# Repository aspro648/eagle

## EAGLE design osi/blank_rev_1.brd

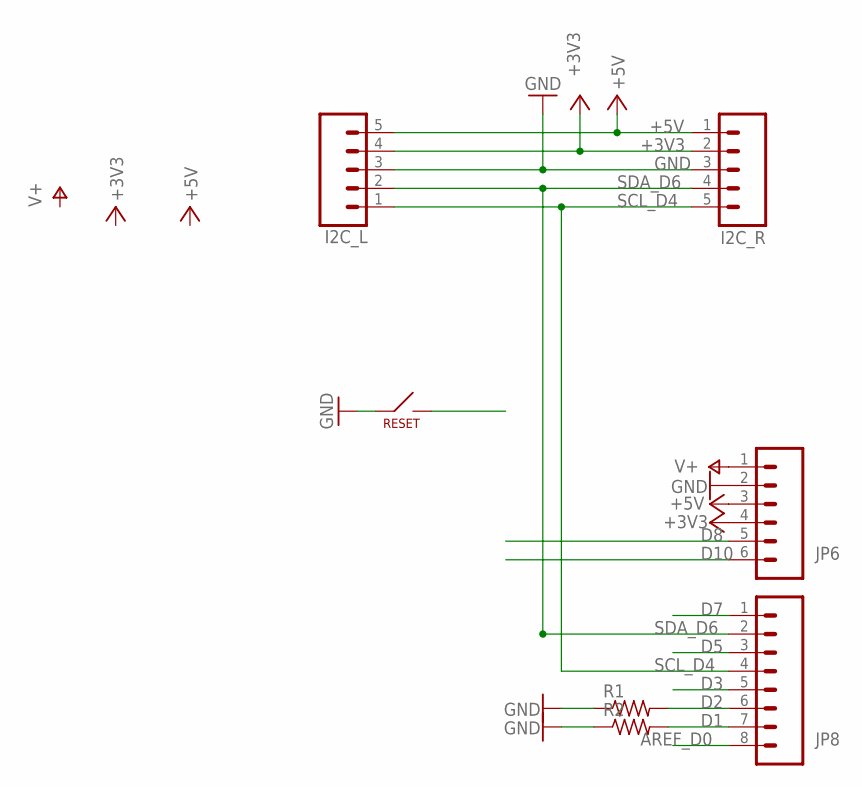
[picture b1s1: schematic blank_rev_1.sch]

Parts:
I2C_L, I2C_R: M05PTH; 1X05
JP6: M06SIP; 1X06
JP8: M081X08; 1X08
R1, R2: R-US_0204/2V; 0204V
RESET: PTS635_SWITCH

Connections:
+3V3: I2C_L.4, I2C_R.2, JP6.4
+5V: I2C_L.5, I2C_R.1, JP6.3
AREF_D0: JP8.8
D1: JP8.7, R2.2
D2: JP8.6, R1.2
D3: JP8.5
D5: JP8.3
D7: JP8.1
D8: JP6.5
D10: JP6.6
GND: I2C_L.3, I2C_R.3, JP6.2, R1.1, R2.1, RESET.P$1
RESET: RESET.P$2
SCL_D4: I2C_L.1, I2C_R.5, JP8.4
SDA_D6: I2C_L.2, I2C_R.4, JP8.2
V+: JP6.1

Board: 2 copper layers, 7 parts (0 on the bottom side), 7 nets, no tracks yet.

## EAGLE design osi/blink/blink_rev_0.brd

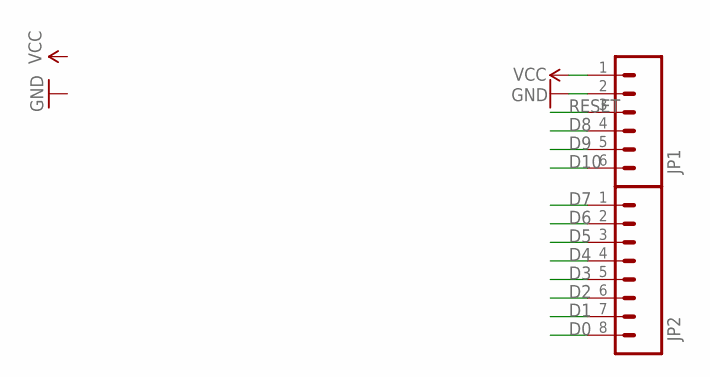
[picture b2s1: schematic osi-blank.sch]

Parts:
JP1: M06SIP; 1X06
JP2: M081X08; 1X08

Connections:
D0: JP2.8; also elsewhere on the board
D1: JP2.7; also elsewhere on the board
D2: JP2.6
D3: JP2.5
D4: JP2.4
D5: JP2.3; also elsewhere on the board
D6: JP2.2; also elsewhere on the board
D7: JP2.1; also elsewhere on the board
D8: JP1.4; also elsewhere on the board
D9: JP1.5
D10: JP1.6
GND: JP1.2; also elsewhere on the board
RESET: JP1.3
VCC: JP1.1; also elsewhere on the board

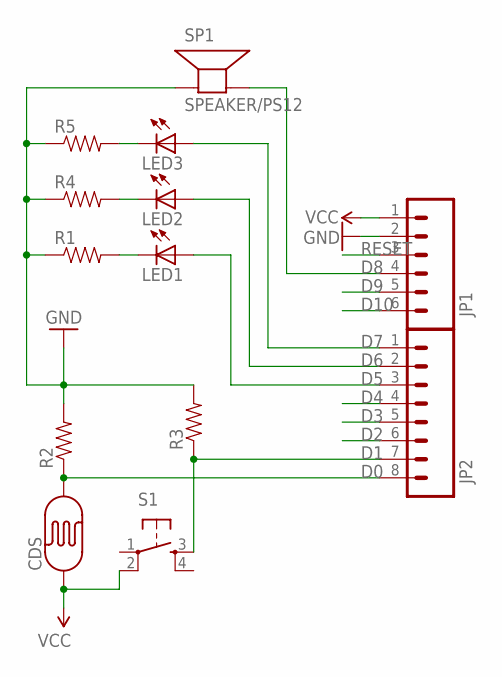
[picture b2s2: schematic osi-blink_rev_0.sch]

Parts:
CDS: PHOTOCELLPTH-KIT; PHOTOCELL-KIT
JP1: M06SIP; 1X06
JP2: M081X08; 1X08
LED1, LED2, LED3: LED3MM
R1, R2, R3, R4, R5: RESISTORKIT; AXIAL-0.3-KIT
S1: TAC_SWITCHPTH; TACTILE-PTH
SP1: SPEAKER/PS12; PS12

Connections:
D0: CDS.2, JP2.8, R2.P$1 (1)
D1: JP2.7, R3.P$1 (1), S1.3
D2: JP2.6
D3: JP2.5
D4: JP2.4
D5: JP2.3, LED1.A
D6: JP2.2, LED2.A
D7: JP2.1, LED3.A
D8: JP1.4, SP1.P$2 (-)
D9: JP1.5
D10: JP1.6
GND: JP1.2, R1.P$1 (1), R2.P$2 (2), R3.P$2 (2), R4.P$1 (1), R5.P$1 (1), SP1.P$1 (+)
unnamed: LED1.K (C), R1.P$2 (2)
unnamed: LED2.K (C), R4.P$2 (2)
unnamed: LED3.K (C), R5.P$2 (2)
RESET: JP1.3
VCC: CDS.1, JP1.1, S1.2

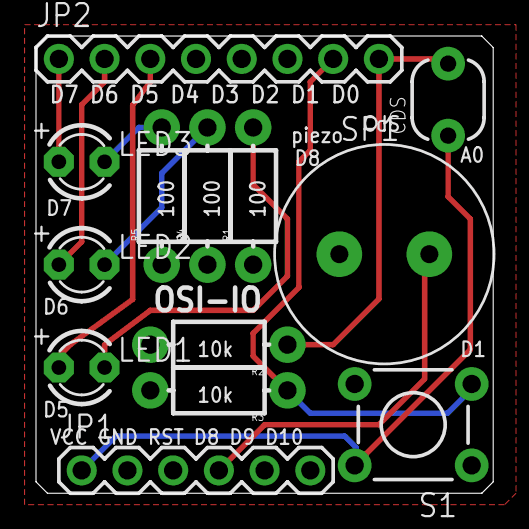
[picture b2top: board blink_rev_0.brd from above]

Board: 2 copper layers, 25.4 x 25.4 mm, 13 parts (0 on the bottom side), 11 nets.

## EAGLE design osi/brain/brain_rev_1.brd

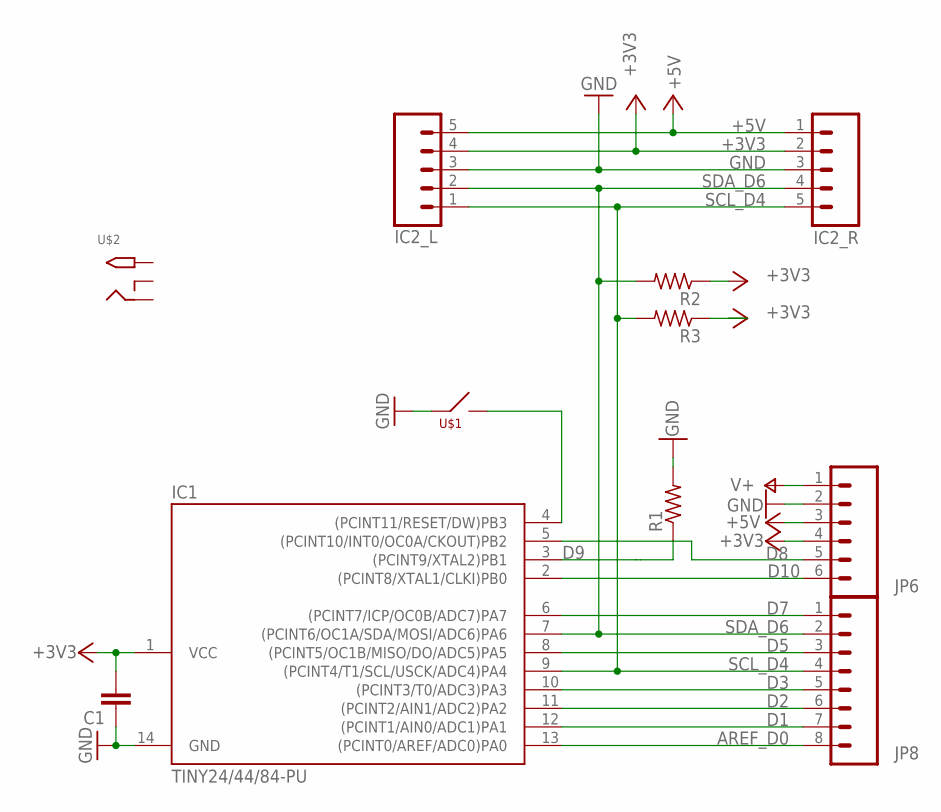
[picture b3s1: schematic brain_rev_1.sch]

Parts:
C1: CAPKIT; CAP-PTH-SMALL-KIT
IC1: TINY24/44/84-PU; DIL14
IC2_L, IC2_R: M05PTH; 1X05
JP6: M06SIP; 1X06
JP8: M081X08; 1X08
R1, R2, R3: R-US_0204/2V; 0204V
U$1: PTS635_SWITCH
U$2: 2.1MMJACKTHM; PJ-102A

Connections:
+3V3: C1.2, IC1.1 (VCC), IC2_L.4, IC2_R.2, JP6.4, R2.1, R3.1
+5V: IC2_L.5, IC2_R.1, JP6.3
AREF_D0: IC1.13 ((PCINT0/AREF/ADC0)PA0), JP8.8
D1: IC1.12 ((PCINT1/AIN0/ADC1)PA1), JP8.7
D2: IC1.11 ((PCINT2/AIN1/ADC2)PA2), JP8.6
D3: IC1.10 ((PCINT3/T0/ADC3)PA3), JP8.5
D5: IC1.8 ((PCINT5/OC1B/MISO/DO/ADC5)PA5), JP8.3
D7: IC1.6 ((PCINT7/ICP/OC0B/ADC7)PA7), JP8.1
D8: IC1.5 ((PCINT10/INT0/OC0A/CKOUT)PB2), JP6.5
D9: IC1.3 ((PCINT9/XTAL2)PB1), R1.1
D10: IC1.2 ((PCINT8/XTAL1/CLKI)PB0), JP6.6
GND: C1.1, IC1.14 (GND), IC2_L.3, IC2_R.3, JP6.2, R1.2, U$1.P$1
RESET: IC1.4 ((PCINT11/RESET/DW)PB3), U$1.P$2
SCL_D4: IC1.9 ((PCINT4/T1/SCL/USCK/ADC4)PA4), IC2_L.1, IC2_R.5, JP8.4, R3.2
SDA_D6: IC1.7 ((PCINT6/OC1A/SDA/MOSI/ADC6)PA6), IC2_L.2, IC2_R.4, JP8.2, R2.2
V+: JP6.1

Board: 2 copper layers, 11 parts (0 on the bottom side), 15 nets, no tracks yet.

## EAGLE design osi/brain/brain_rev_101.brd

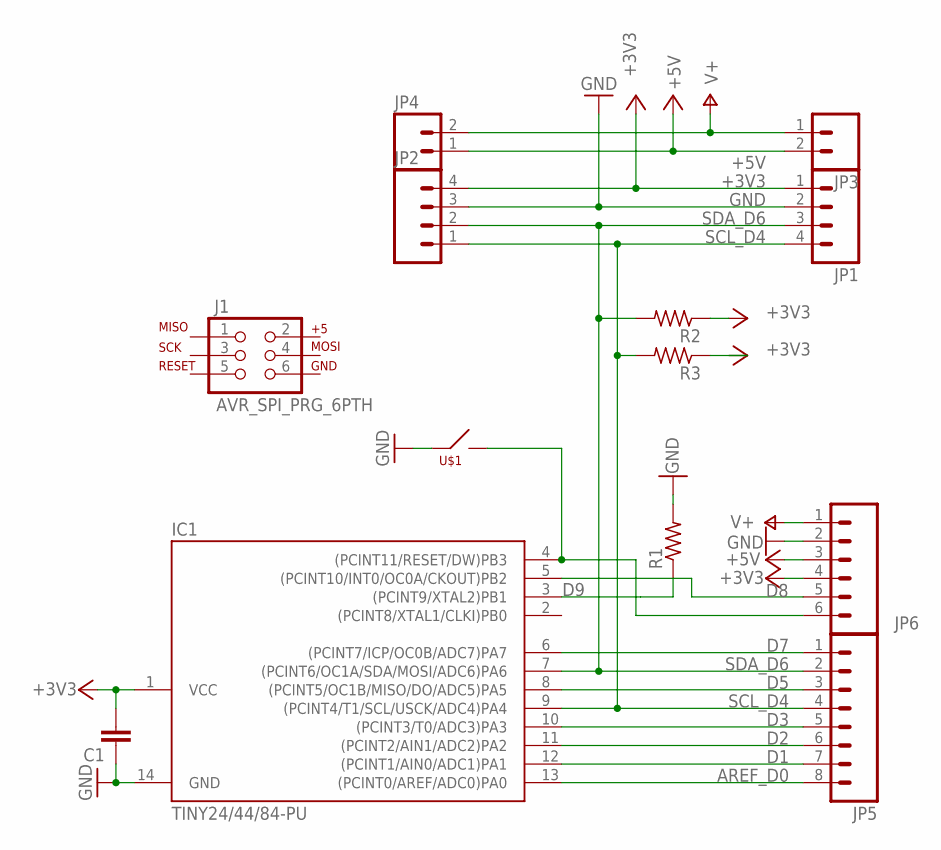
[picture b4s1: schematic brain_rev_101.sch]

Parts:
C1: CAPKIT; CAP-PTH-SMALL-KIT
IC1: TINY24/44/84-PU; DIL14
J1: AVR_SPI_PRG_6PTH; 2X3
JP1, JP2: M04PTH; 1X04
JP3, JP4: M02PTH; 1X02
JP5: M081X08; 1X08
JP6: M06SIP; 1X06
R1, R2, R3: R-US_0204/2V; 0204V
U$1: PTS635_SWITCH

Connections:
+3V3: C1.2, IC1.1 (VCC), JP1.1, JP2.4, JP6.4, R2.1, R3.1
+5V: JP3.2, JP4.1, JP6.3
AREF_D0: IC1.13 ((PCINT0/AREF/ADC0)PA0), JP5.8
D1: IC1.12 ((PCINT1/AIN0/ADC1)PA1), JP5.7
D2: IC1.11 ((PCINT2/AIN1/ADC2)PA2), JP5.6
D3: IC1.10 ((PCINT3/T0/ADC3)PA3), JP5.5
D5: IC1.8 ((PCINT5/OC1B/MISO/DO/ADC5)PA5), JP5.3
D7: IC1.6 ((PCINT7/ICP/OC0B/ADC7)PA7), JP5.1
D8: IC1.5 ((PCINT10/INT0/OC0A/CKOUT)PB2), JP6.5
D9: IC1.3 ((PCINT9/XTAL2)PB1), R1.1
GND: C1.1, IC1.14 (GND), JP1.2, JP2.3, JP6.2, R1.2, U$1.P$1
RESET: IC1.4 ((PCINT11/RESET/DW)PB3), JP6.6, U$1.P$2
SCL_D4: IC1.9 ((PCINT4/T1/SCL/USCK/ADC4)PA4), JP1.4, JP2.1, JP5.4, R3.2
SDA_D6: IC1.7 ((PCINT6/OC1A/SDA/MOSI/ADC6)PA6), JP1.3, JP2.2, JP5.2, R2.2
V+: JP3.1, JP4.2, JP6.1

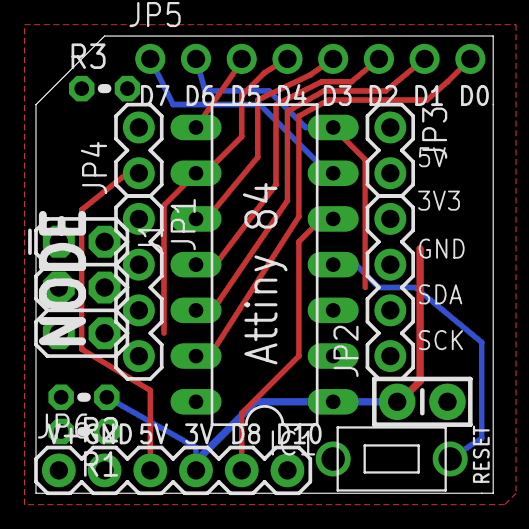
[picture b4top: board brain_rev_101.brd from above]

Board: 2 copper layers, 25.4 x 25.4 mm, 13 parts (0 on the bottom side), 15 nets.

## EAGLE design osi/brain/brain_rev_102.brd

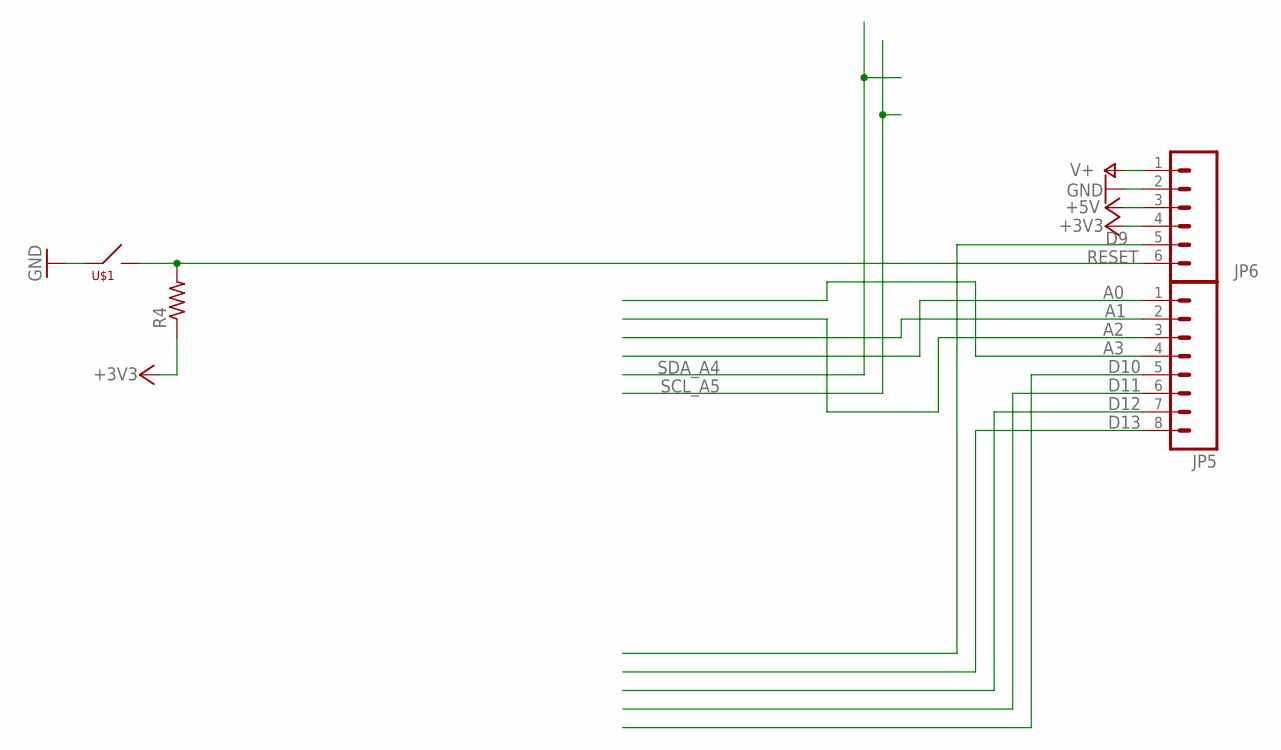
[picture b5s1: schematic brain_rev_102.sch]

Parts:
JP5: M081X08; 1X08
JP6: M06SIP; 1X06
R4: R-US_0204/2V; 0204V
U$1: PTS635_SWITCH

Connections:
+3V3: JP6.4, R4.1
+5V: JP6.3
A0: JP5.4
A1: JP5.3
A2: JP5.2
A3: JP5.1
D9: JP6.5
D10: JP5.8
D11: JP5.7
D12: JP5.6
D13: JP5.5
GND: JP6.2, U$1.P$1
RESET: JP6.6, R4.2, U$1.P$2
V+: JP6.1

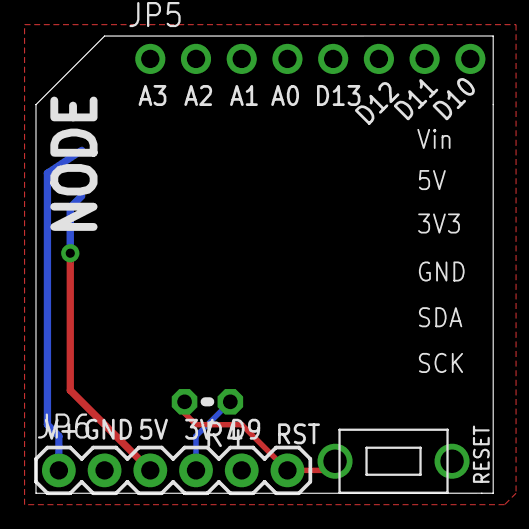
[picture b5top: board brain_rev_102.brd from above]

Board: 2 copper layers, 25.4 x 25.4 mm, 4 parts (0 on the bottom side), 3 nets.

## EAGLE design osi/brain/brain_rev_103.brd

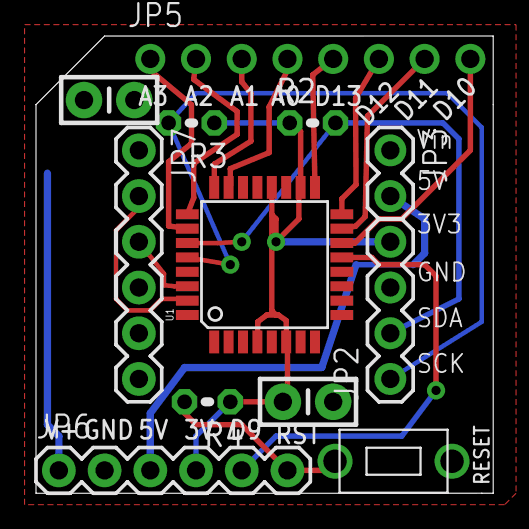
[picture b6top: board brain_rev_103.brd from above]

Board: 2 copper layers, 25.4 x 25.4 mm, 12 parts (0 on the bottom side), 19 nets.

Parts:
C1, C2: CAP-PTH-SMALL-KIT
JP2: 1X04
JP3: 1X02
JP5: 1X08
JP6: 1X06
JP7: FTDI Basic; 1X06
R2, R3, R4: 0204V
U1: ATMEGA168; TQFP32-08
U$1: PTS635_SWITCH

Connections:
+3V3: C1.2, JP2.4, JP6.4, JP7.4, R2.1, R3.1, R4.1, U1.4, U1.6, U1.18, U1.20
+5V: JP3.2, JP6.3
A0: JP5.4, U1.23
A1: JP5.3, U1.24
A2: JP5.2, U1.25
A3: JP5.1, U1.26
D9: JP6.5, U1.13
D10: JP5.8, U1.14
D11: JP5.7, U1.15
D12: JP5.6, U1.16
D13: JP5.5, U1.17
DTR: C2.2, JP7.1
GND: C1.1, JP2.3, JP6.2, JP7.5, JP7.6, U1.3, U1.5, U1.21, U$1.P$1
RESET: C2.1, JP6.6, R4.2, U1.29, U$1.P$2
RXI: JP7.3, U1.30
SCL_A5: JP2.1, R3.2, U1.28
SDA_A4: JP2.2, R2.2, U1.27
TXO: JP7.2, U1.31
V+: JP3.1, JP6.1

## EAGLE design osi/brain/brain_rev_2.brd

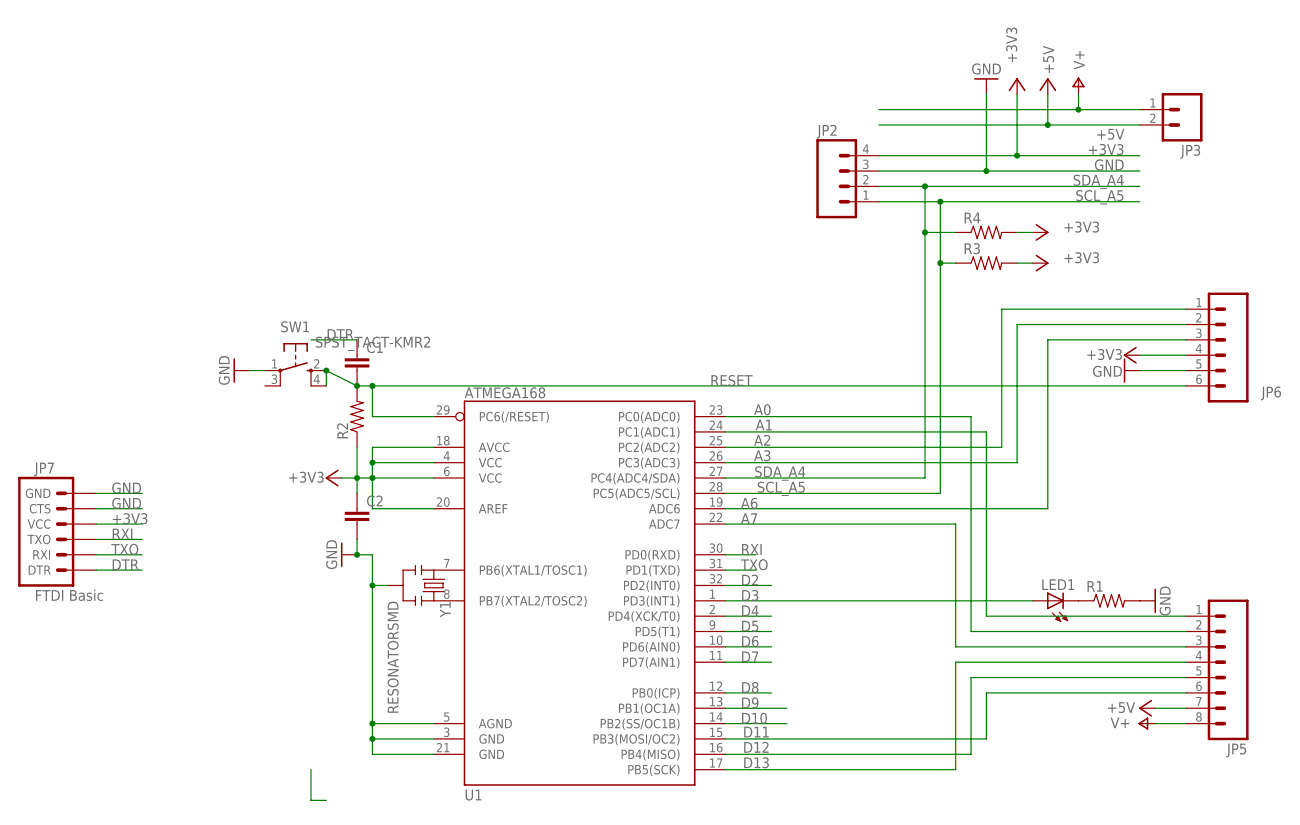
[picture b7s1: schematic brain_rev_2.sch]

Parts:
C1, C2: CAP1206; 1206
JP2: M04PTH; 1X04
JP3: M02PTH; 1X02
JP5: M081X08; 1X08
JP6: M06SIP; 1X06
JP7: FTDI Basic; 1X06
LED1: LEDCHIPLED_1206; CHIPLED_1206
R1, R2, R3, R4: RESISTOR1206; 1206
SW1: SPST_TACT-KMR2; KMR2
U1: ATMEGA168; TQFP32-08
Y1: RESONATORSMD; RESONATOR-SMD

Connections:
+3V3: C2.1, JP2.4, JP6.4, JP7.4 (VCC), R2.1, R3.2, R4.2, U1.4 (VCC), U1.6 (VCC), U1.18 (AVCC), U1.20 (AREF)
+5V: JP3.2, JP5.7
A0: JP5.2, U1.23 (PC0(ADC0))
A1: JP5.1, U1.24 (PC1(ADC1))
A2: JP6.1, U1.25 (PC2(ADC2))
A3: JP6.2, U1.26 (PC3(ADC3))
A6: JP6.3, U1.19 (ADC6)
A7: JP5.3, U1.22 (ADC7)
D2: U1.32 (PD2(INT0))
D3: LED1.A, U1.1 (PD3(INT1))
D4: U1.2 (PD4(XCK/T0))
D5: U1.9 (PD5(T1))
D6: U1.10 (PD6(AIN0))
D7: U1.11 (PD7(AIN1))
D8: U1.12 (PB0(ICP))
D9: U1.13 (PB1(OC1A))
D10: U1.14 (PB2(SS/OC1B))
D11: JP5.6, U1.15 (PB3(MOSI/OC2))
D12: JP5.5, U1.16 (PB4(MISO))
D13: JP5.4, U1.17 (PB5(SCK))
DTR: C1.1, JP7.1 (DTR)
GND: C2.2, JP2.3, JP6.5, JP7.5 (CTS), JP7.6 (GND), R1.2, SW1.1, U1.3 (GND), U1.5 (AGND), U1.21 (GND), Y1.2
unnamed: U1.8 (PB7(XTAL2/TOSC2)), Y1.3
unnamed: U1.7 (PB6(XTAL1/TOSC1)), Y1.1
unnamed: LED1.C, R1.1
RESET: C1.2, JP6.6, R2.2, SW1.2 (S), SW1.4 (S1), U1.29 (PC6(/RESET))
RXI: JP7.3 (TXO), U1.30 (PD0(RXD))
SCL_A5: JP2.1, R3.1, U1.28 (PC5(ADC5/SCL))
SDA_A4: JP2.2, R4.1, U1.27 (PC4(ADC4/SDA))
TXO: JP7.2 (RXI), U1.31 (PD1(TXD))
V+: JP3.1, JP5.8

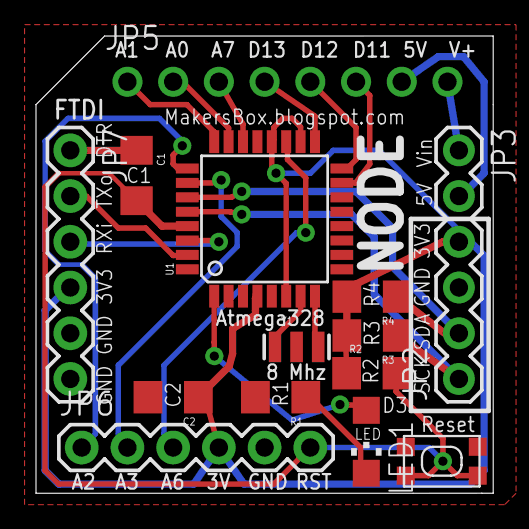
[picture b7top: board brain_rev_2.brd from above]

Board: 2 copper layers, 25.4 x 25.4 mm, 16 parts (0 on the bottom side), 23 nets.

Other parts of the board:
U$1: OSHWLOGO_TOL_0.2

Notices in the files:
parts and their libraries:
SparkFun_mod: Licensing: CC v3.0 Share-Alike You are welcome to use this library for commercial purposes.
